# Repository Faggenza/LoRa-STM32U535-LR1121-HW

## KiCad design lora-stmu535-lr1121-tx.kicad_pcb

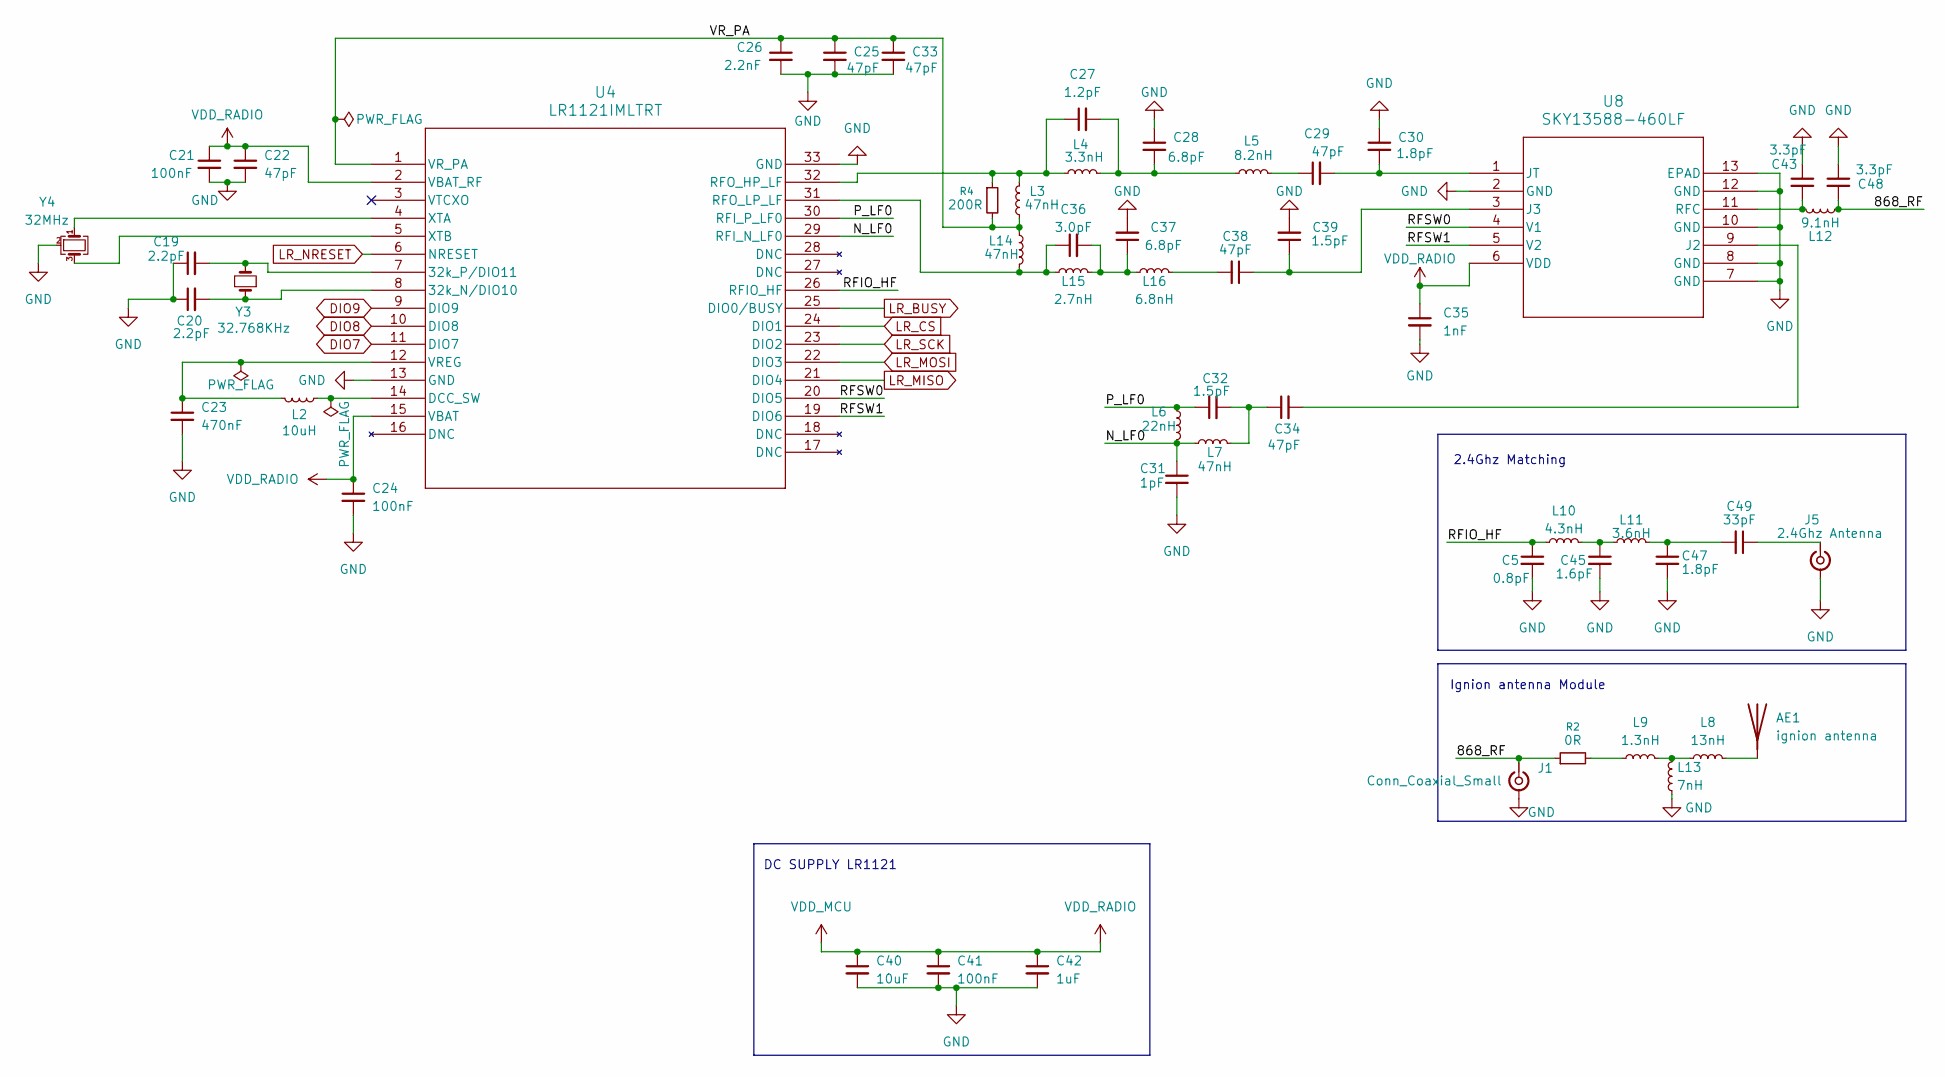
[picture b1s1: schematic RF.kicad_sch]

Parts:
AE1: ignion antenna; igiion_868
C5: 0.8pF; C_0201_0603Metric
C19, C20: 2.2pF; C_0402_1005Metric_Pad0.74x0.62mm_HandSolder
C21, C24, C41: 100nF; C_0402_1005Metric_Pad0.74x0.62mm_HandSolder
C22: 47pF; C_0402_1005Metric_Pad0.74x0.62mm_HandSolder
C23: 470nF; C_0402_1005Metric_Pad0.74x0.62mm_HandSolder
C25, C29, C33, C34, C38: 47pF; C_0201_0603Metric
C26: 2.2nF; C_0201_0603Metric
C27: 1.2pF; C_0201_0603Metric
C28, C37: 6.8pF; C_0201_0603Metric
C30, C47: 1.8pF; C_0201_0603Metric
C31: 1pF; C_0201_0603Metric
C32, C39: 1.5pF; C_0201_0603Metric
C35: 1nF; C_0201_0603Metric
C36: 3.0pF; C_0201_0603Metric
C40: 10uF; C_0603_1608Metric_Pad1.08x0.95mm_HandSolder
C42: 1uF; C_0402_1005Metric_Pad0.74x0.62mm_HandSolder
C43, C48: 3.3pF; C_0201_0603Metric
C45: 1.6pF; C_0201_0603Metric
C49: 33pF; C_0201_0603Metric
J1: Conn_Coaxial_Small; U.FL_Molex_MCRF_73412-0110_Vertical
J5: 2.4Ghz Antenna; U.FL_Molex_MCRF_73412-0110_Vertical
L2: 10uH; L_0603_1608Metric_Pad1.05x0.95mm_HandSolder
L3, L7, L14: 47nH; L_0201_0603Metric
L4: 3.3nH; L_0201_0603Metric
L5: 8.2nH; L_0201_0603Metric
L6: 22nH; L_0201_0603Metric
L8: 13nH; L_0402_1005Metric_Pad0.77x0.64mm_HandSolder
L9: 1.3nH; L_0402_1005Metric_Pad0.77x0.64mm_HandSolder
L10: 4.3nH; L_0201_0603Metric
L11: 3.6nH; L_0201_0603Metric
L12: 9.1nH; L_0201_0603Metric
L13: 7nH; L_0402_1005Metric_Pad0.77x0.64mm_HandSolder
L15: 2.7nH; L_0201_0603Metric
L16: 6.8nH; L_0201_0603Metric
R2: 0R; R_0603_1608Metric_Pad0.98x0.95mm_HandSolder
R4: 200R; R_0201_0603Metric
U4: LR1121IMLTRT; QFN32_5X5_MLP_SEM
U8: SKY13588-460LF; QFN12_SKY-L
Y3: 32.768KHz; Crystal_SMD_2012-2Pin_2.0x1.2mm_HandSoldering
Y4: 32MHz; Crystal_SMD_2016-4Pin_2.0x1.6mm

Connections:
/RF/868_RF: C48.2, J1.1 (In), L12.2, R2.1
/RF/N_LF0: C31.1, L6.2, L7.1, U4.29 (RFI_N_LF0)
/RF/P_LF0: C32.1, L6.1, U4.30 (RFI_P_LF0)
/RF/RFIO_HF: C5.1, L10.1, U4.26 (RFIO_HF)
/RF/RFSW0: U4.20 (DIO5), U8.4 (V1)
/RF/RFSW1: U4.19 (DIO6), U8.5 (V2)
/RF/VR_PA: C25.1, C26.1, C33.1, L3.1, L14.1, R4.2, U4.1 (VR_PA)
DIO7: U4.11 (DIO7); also elsewhere on the board
DIO8: U4.10 (DIO8); also elsewhere on the board
DIO9: U4.9 (DIO9); also elsewhere on the board
GND: AE1.2, C5.2, C19.1, C20.1, C21.2, C22.2, C23.2, C24.2, C25.2, C26.2, C28.1, C30.1, C31.2, C33.2, C35.2, C37.2, C39.2, C40.2, C41.2, C42.2, C43.1, C45.2, C47.2, C48.1, J1.2 (Ext), J5.2 (Ext), L13.1, U4.13 (GND), U4.33 (GND), U8.2 (GND), U8.7 (GND), U8.8 (GND), U8.10 (GND), U8.12 (GND), U8.13 (EPAD), Y4.2 (G), Y4.4 (G); also elsewhere on the board
LR_BUSY: U4.25 (DIO0/BUSY); also elsewhere on the board
LR_CS: U4.24 (DIO1); also elsewhere on the board
LR_MISO: U4.21 (DIO4); also elsewhere on the board
LR_MOSI: U4.22 (DIO3); also elsewhere on the board
LR_NRESET: U4.6 (NRESET); also elsewhere on the board
LR_SCK: U4.23 (DIO2); also elsewhere on the board
unnamed: C27.2, C28.2, L4.2, L5.1
unnamed: C29.1, L5.2
unnamed: C32.2, C34.1, L7.2
unnamed: C36.2, C37.1, L15.2, L16.1
unnamed: C38.2, L16.2
unnamed: C45.1, L10.2, L11.1
unnamed: C47.1, C49.2, L11.2
unnamed: C49.1, J5.1 (In)
unnamed: L8.1, L9.2, L13.2
unnamed: C20.2, U4.8 (32k_N/DIO10), Y3.1
unnamed: C19.2, U4.7 (32k_P/DIO11), Y3.2
unnamed: L2.1, U4.14 (DCC_SW)
unnamed: C27.1, L3.2, L4.1, R4.1, U4.32 (RFO_HP_LF)
unnamed: C36.1, L14.2, L15.1, U4.31 (RFO_LP_LF)
unnamed: C23.1, L2.2, U4.12 (VREG)
unnamed: U4.4 (XTA), Y4.1
unnamed: U4.5 (XTB), Y4.3
unnamed: C34.2, U8.9 (J2)
unnamed: C38.1, C39.1, U8.3 (J3)
unnamed: C29.2, C30.2, U8.1 (JT)
unnamed: C43.2, L12.1, U8.11 (RFC)
VBAT: C21.1, C22.1, C24.1, C35.1, C40.1, C41.1, C42.1, U4.2 (VBAT_RF), U4.15 (VBAT), U8.6 (VDD); also elsewhere on the board

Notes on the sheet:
2.4Ghz Matching
DC SUPPLY LR1121
Ignion antenna Module

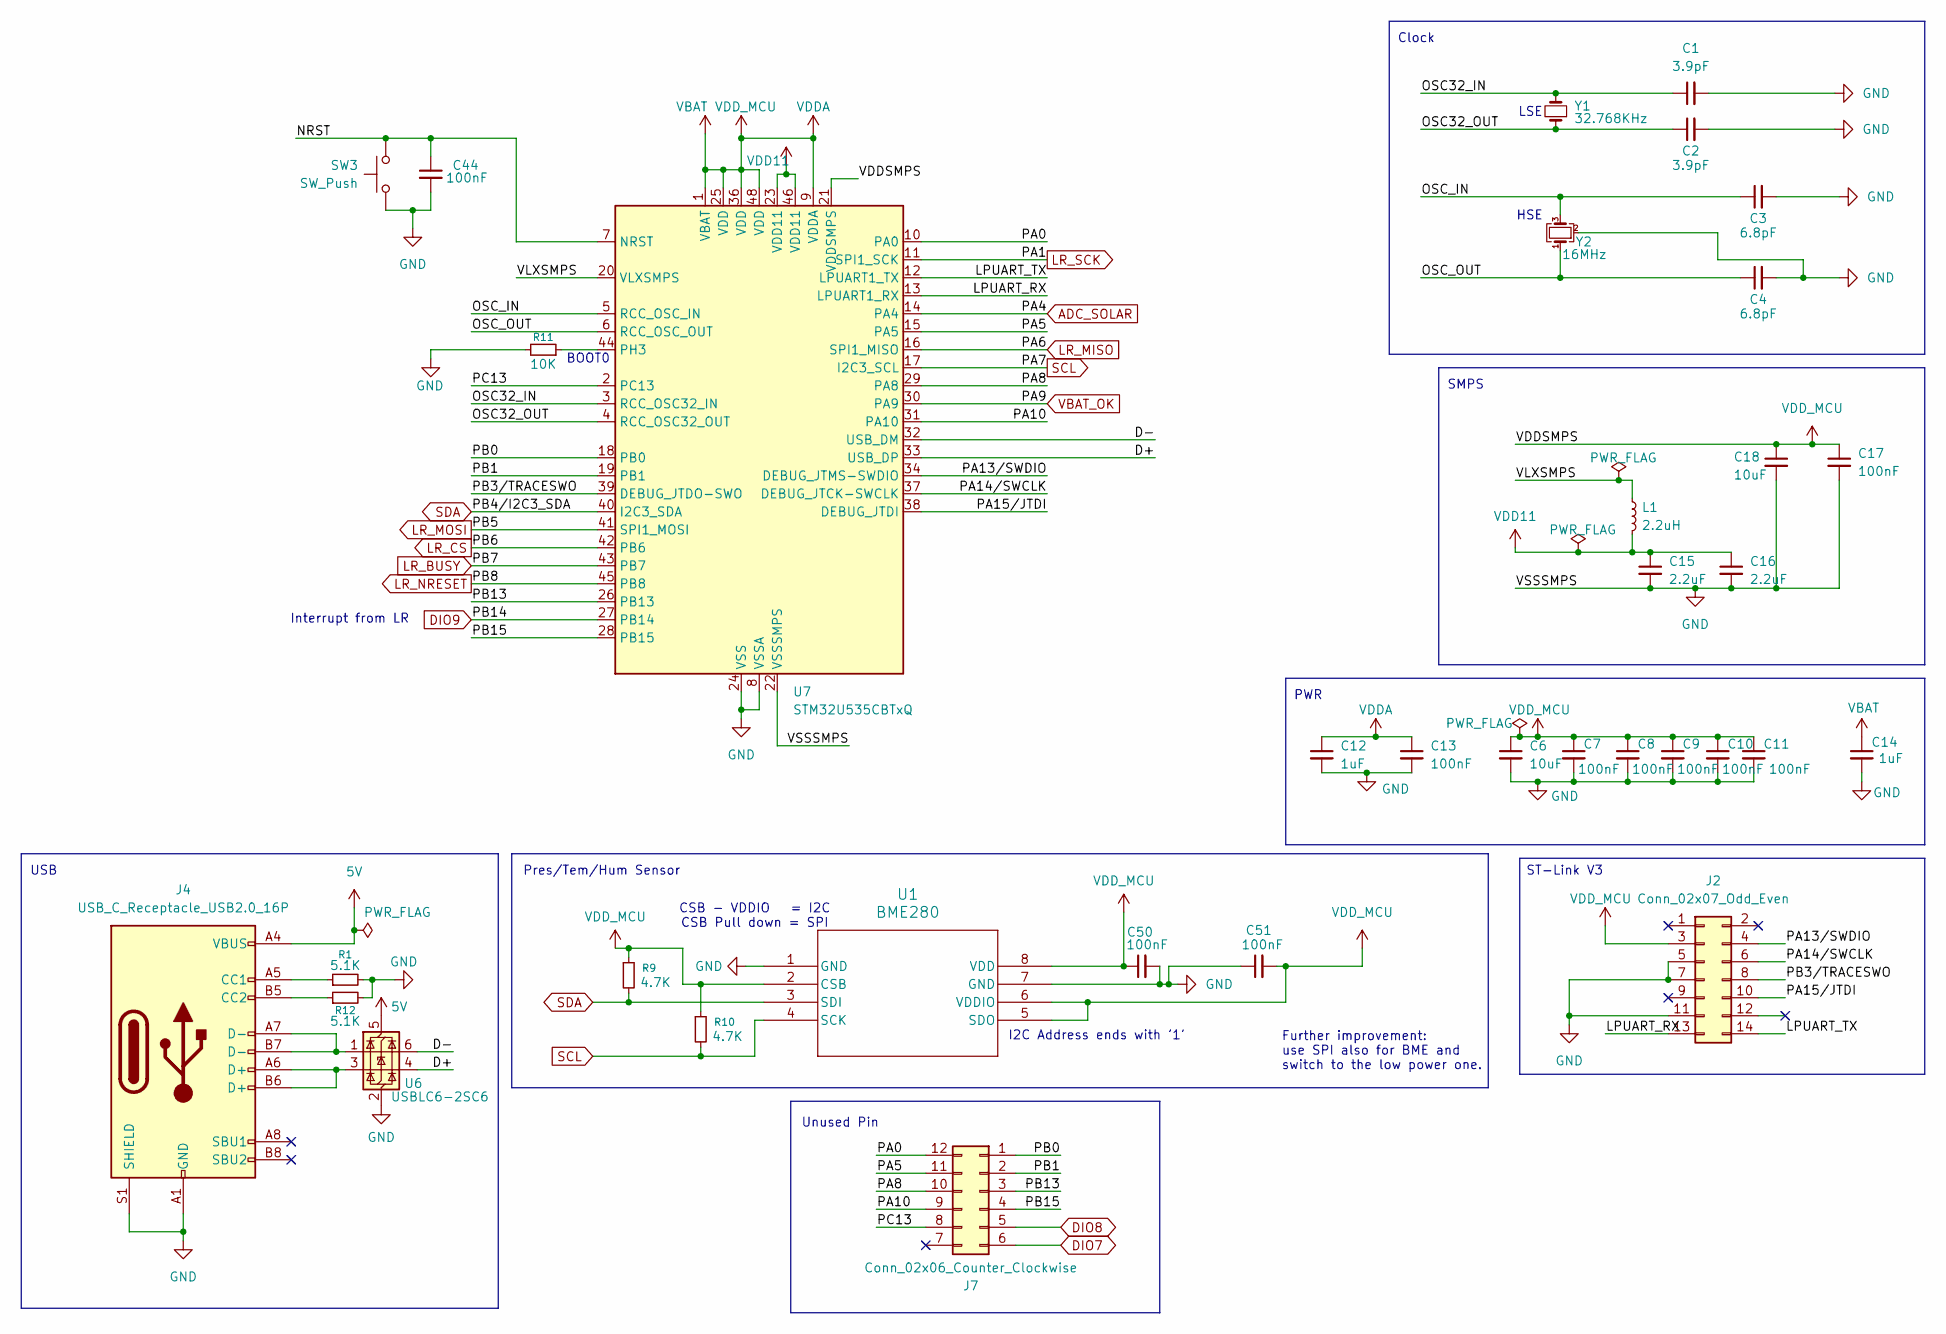
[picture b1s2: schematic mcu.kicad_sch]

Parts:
C1, C2: 3.9pF; C_0402_1005Metric_Pad0.74x0.62mm_HandSolder
C3, C4: 6.8pF; C_0402_1005Metric_Pad0.74x0.62mm_HandSolder
C6, C18: 10uF; C_0603_1608Metric_Pad1.08x0.95mm_HandSolder
C7, C8, C9, C10, C11, C13, C17, C44, C50, C51: 100nF; C_0402_1005Metric_Pad0.74x0.62mm_HandSolder
C12, C14: 1uF; C_0603_1608Metric_Pad1.08x0.95mm_HandSolder
C15, C16: 2.2uF; C_0603_1608Metric_Pad1.08x0.95mm_HandSolder
J2: Conn_02x07_Odd_Even; PinHeader_2x07_P1.27mm_Vertical_SMD
J4: USB_C_Receptacle_USB2.0_16P; USB_C_Receptacle_G-Switch_GT-USB-7010ASV
J7: Conn_02x06_Counter_Clockwise; PinHeader_2x06_P2.54mm_Vertical
L1: 2.2uH; L_0805_2012Metric_Pad1.05x1.20mm_HandSolder
R1, R12: 5.1K; R_0402_1005Metric_Pad0.72x0.64mm_HandSolder
R9, R10: 4.7K; R_0402_1005Metric_Pad0.72x0.64mm_HandSolder
R11: 10K; R_0402_1005Metric_Pad0.72x0.64mm_HandSolder
SW3: SW_Push; SW_SPST_B3U-1000P
U1: BME280; DFN8_0p65_2p5SQ_BOS
U6: USBLC6-2SC6; SOT-666
U7: STM32U535CBTxQ; LQFP-48_7x7mm_P0.5mm
Y1: 32.768KHz; Crystal_SMD_MicroCrystal_CM9V-T1A-2Pin_1.6x1.0mm_HandSolder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
Y2: 16MHz; Crystal_SMD_2016-4Pin_2.0x1.6mm

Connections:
5V: J4.A4 (VBUS), J4.A9 (VBUS), J4.B4 (VBUS), J4.B9 (VBUS), U6.5 (VBUS); also elsewhere on the board
/MCU/D+: U6.4 (I/O2), U7.33 (USB_DP)
/MCU/D-: U6.6 (I/O1), U7.32 (USB_DM)
/MCU/LPUART_RX: J2.13, U7.13 (LPUART1_RX)
/MCU/LPUART_TX: J2.14, U7.12 (LPUART1_TX)
/MCU/NRST: C44.1, SW3.1, U7.7 (NRST)
/MCU/OSC32_IN: C1.1, U7.3 (RCC_OSC32_IN), Y1.2
/MCU/OSC32_OUT: C2.1, U7.4 (RCC_OSC32_OUT), Y1.1
/MCU/OSC_IN: C3.1, U7.5 (RCC_OSC_IN), Y2.3
/MCU/OSC_OUT: C4.1, U7.6 (RCC_OSC_OUT), Y2.1
/MCU/PA0: J7.12, U7.10 (PA0)
/MCU/PA5: J7.11, U7.15 (PA5)
/MCU/PA8: J7.10, U7.29 (PA8)
/MCU/PA10: J7.9, U7.31 (PA10)
/MCU/PA13/SWDIO: J2.4, U7.34 (DEBUG_JTMS-SWDIO)
/MCU/PA14/SWCLK: J2.6, U7.37 (DEBUG_JTCK-SWCLK)
/MCU/PA15/JTDI: J2.10, U7.38 (DEBUG_JTDI)
/MCU/PB0: J7.1, U7.18 (PB0)
/MCU/PB1: J7.2, U7.19 (PB1)
/MCU/PB3/TRACESWO: J2.8, U7.39 (DEBUG_JTDO-SWO)
/MCU/PB13: J7.3, U7.26 (PB13)
/MCU/PB15: J7.4, U7.28 (PB15)
/MCU/PC13: J7.8, U7.2 (PC13)
/MCU/VLXSMPS: L1.1, U7.20 (VLXSMPS)
ADC_SOLAR: U7.14 (PA4); also elsewhere on the board
DIO7: J7.6; also elsewhere on the board
DIO8: J7.5; also elsewhere on the board
DIO9: U7.27 (PB14); also elsewhere on the board
GND: C1.2, C2.2, C3.2, C4.2, C6.2, C7.2, C8.2, C9.2, C10.2, C11.2, C12.2, C13.2, C14.2, C15.2, C16.2, C17.2, C18.2, C44.2, C50.2, C51.1, J2.5, J2.7, J2.11, J4.A1 (GND), J4.A12 (GND), J4.B1 (GND), J4.B12 (GND), J4.S1 (SHIELD), R1.2, R11.2, R12.2, SW3.2, U1.1 (GND), U1.7 (GND), U6.2 (GND), U7.8 (VSSA), U7.22 (VSSSMPS), U7.24 (VSS), U7.35 (VSS), U7.47 (VSS), Y2.2 (G), Y2.4 (G); also elsewhere on the board
LR_BUSY: U7.43 (PB7); also elsewhere on the board
LR_CS: U7.42 (PB6); also elsewhere on the board
LR_MISO: U7.16 (SPI1_MISO); also elsewhere on the board
LR_MOSI: U7.41 (SPI1_MOSI); also elsewhere on the board
LR_NRESET: U7.45 (PB8); also elsewhere on the board
LR_SCK: U7.11 (SPI1_SCK); also elsewhere on the board
unnamed: J4.A5 (CC1), R1.1
unnamed: J4.B5 (CC2), R12.1
unnamed: J4.A6 (D+), J4.B6 (D+), U6.3 (I/O2)
unnamed: J4.A7 (D-), J4.B7 (D-), U6.1 (I/O1)
unnamed: R11.1, U7.44 (PH3)
SCL: R10.2, U1.4 (SCK), U7.17 (I2C3_SCL)
SDA: R9.2, U1.3 (SDI), U7.40 (I2C3_SDA)
VBAT: C6.1, C7.1, C8.1, C9.1, C10.1, C11.1, C12.1, C13.1, C14.1, C17.1, C18.1, C50.1, C51.2, J2.3, R9.1, R10.1, U1.2 (CSB), U1.5 (SDO), U1.6 (VDDIO), U1.8 (VDD), U7.1 (VBAT), U7.9 (VDDA), U7.21 (VDDSMPS), U7.25 (VDD), U7.36 (VDD), U7.48 (VDD); also elsewhere on the board
VBAT_OK: U7.30 (PA9); also elsewhere on the board
VDD11: C15.1, C16.1, L1.2, U7.23 (VDD11), U7.46 (VDD11)

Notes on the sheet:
Further improvement: use SPI also for BME and switch to the low power one.
BOOT0
I2C Address ends with '1'
Clock
LSE
HSE
SMPS
Interrupt from LR
CSB - VDDIO = I2C CSB Pull down = SPI
ST-Link V3
Pres/Tem/Hum Sensor
PWR
Unused Pin
USB

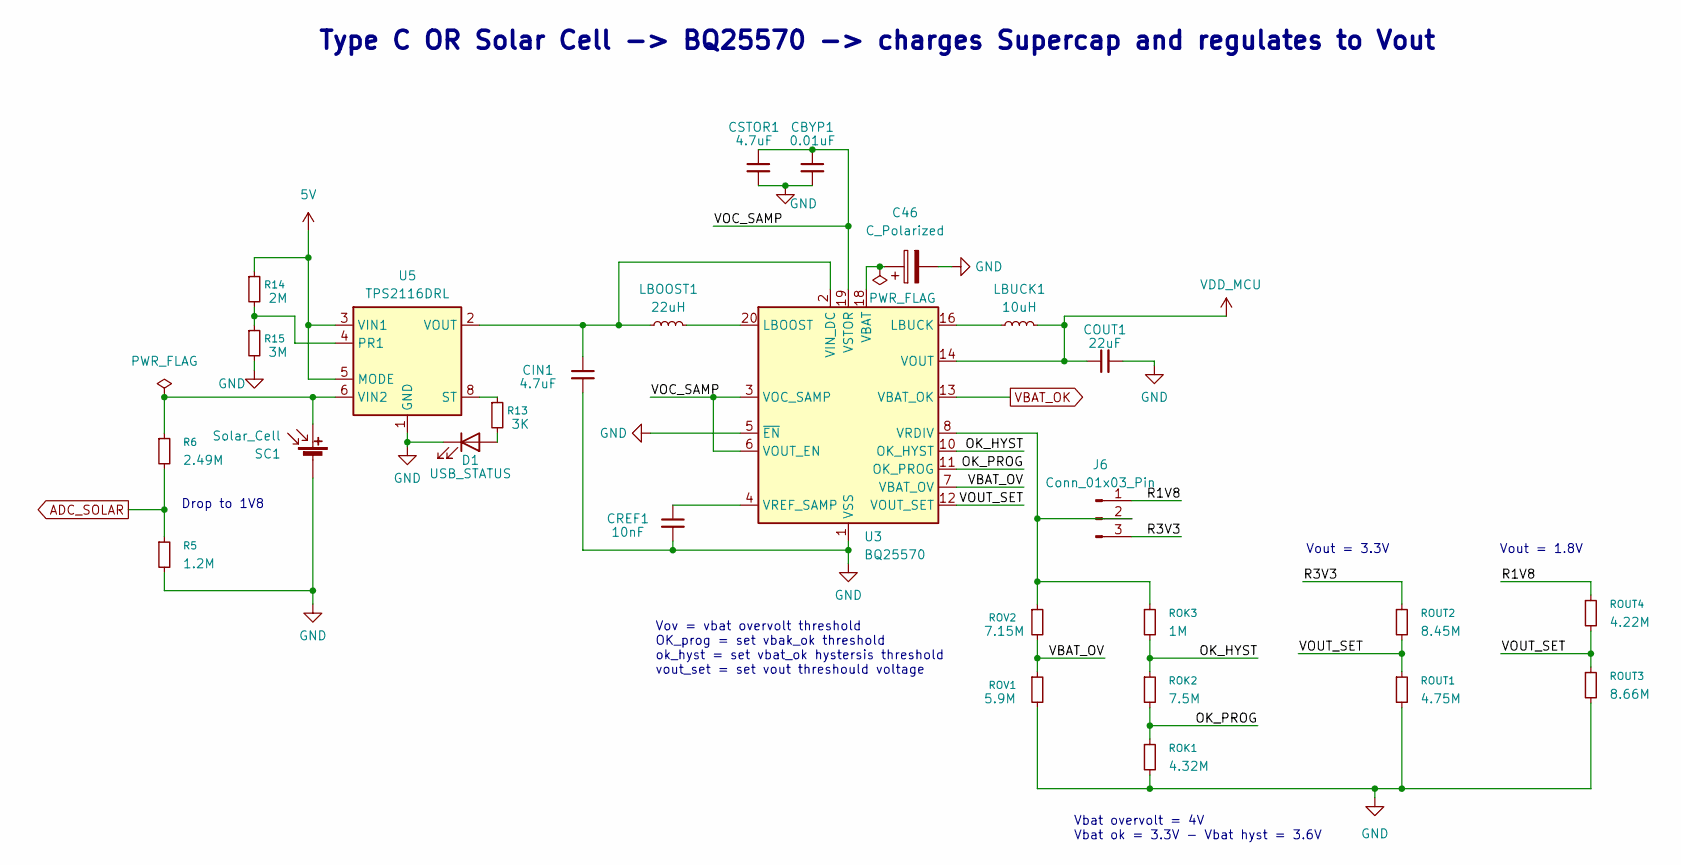
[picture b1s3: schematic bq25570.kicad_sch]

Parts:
C46: C_Polarized; PinHeader_1x02_P2.54mm_Vertical
CBYP1: 0.01uF; C_0402_1005Metric_Pad0.74x0.62mm_HandSolder
CIN1: 4.7uF; C_0603_1608Metric_Pad1.08x0.95mm_HandSolder
COUT1: 22uF; C_0603_1608Metric_Pad1.08x0.95mm_HandSolder
CREF1: 10nF; C_0402_1005Metric_Pad0.74x0.62mm_HandSolder
CSTOR1: 4.7uF; C_0603_1608Metric_Pad1.08x0.95mm_HandSolder
D1: USB_STATUS; LED_0402_1005Metric_Pad0.77x0.64mm_HandSolder
J6: Conn_01x03_Pin; PinHeader_1x03_P2.54mm_Vertical
LBOOST1: 22uH; L_0402_1005Metric_Pad0.77x0.64mm_HandSolder
LBUCK1: 10uH; L_0603_1608Metric_Pad1.05x0.95mm_HandSolder
R5: 1.2M; R_0402_1005Metric_Pad0.72x0.64mm_HandSolder
R6: 2.49M; R_0402_1005Metric_Pad0.72x0.64mm_HandSolder
R13: 3K; R_0402_1005Metric_Pad0.72x0.64mm_HandSolder
R14: 2M; R_0402_1005Metric_Pad0.72x0.64mm_HandSolder
R15: 3M; R_0402_1005Metric_Pad0.72x0.64mm_HandSolder
ROK1: 4.32M; R_0402_1005Metric_Pad0.72x0.64mm_HandSolder
ROK2: 7.5M; R_0402_1005Metric_Pad0.72x0.64mm_HandSolder
ROK3: 1M; R_0402_1005Metric_Pad0.72x0.64mm_HandSolder
ROUT1: 4.75M; R_0402_1005Metric_Pad0.72x0.64mm_HandSolder
ROUT2: 8.45M; R_0402_1005Metric_Pad0.72x0.64mm_HandSolder
ROUT3: 8.66M; R_0402_1005Metric_Pad0.72x0.64mm_HandSolder
ROUT4: 4.22M; R_0402_1005Metric_Pad0.72x0.64mm_HandSolder
ROV1: 5.9M; R_0402_1005Metric_Pad0.72x0.64mm_HandSolder
ROV2: 7.15M; R_0402_1005Metric_Pad0.72x0.64mm_HandSolder
SC1: Solar_Cell; PinHeader_1x02_P2.54mm_Vertical
U3: BQ25570; QFN-20-1EP_3.5x3.5mm_P0.5mm_EP2x2mm
U5: TPS2116DRL; SOT-583-8

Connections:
5V: R14.1, U5.3 (VIN1), U5.5 (MODE); also elsewhere on the board
/BQ25570/OK_HYST: ROK2.1, ROK3.2, U3.10 (OK_HYST)
/BQ25570/OK_PROG: ROK1.1, ROK2.2, U3.11 (OK_PROG)
/BQ25570/R1V8: J6.1 (1.8), ROUT4.1
/BQ25570/R3V3: J6.3 (3.3), ROUT2.1
/BQ25570/VBAT_OV: ROV1.1, ROV2.2, U3.7 (VBAT_OV)
/BQ25570/VOC_SAMP: CBYP1.1, CSTOR1.1, U3.3 (VOC_SAMP), U3.6 (VOUT_EN), U3.19 (VSTOR)
/BQ25570/VOUT_SET: ROUT1.1, ROUT2.2, ROUT3.1, ROUT4.2, U3.12 (VOUT_SET)
ADC_SOLAR: R5.1, R6.2; also elsewhere on the board
GND: C46.2, CBYP1.2, CIN1.2, COUT1.2, CREF1.2, CSTOR1.2, D1.1 (K), R5.2, R15.2, ROK1.2, ROUT1.2, ROUT3.2, ROV1.2, SC1.2 (-), U3.1 (VSS), U3.5 (~EN), U3.9 (VSS), U3.15 (VSS), U3.17 (VSS), U3.21 (VSS), U5.1 (GND); also elsewhere on the board
unnamed: D1.2 (A), R13.2
unnamed: J6.2, ROK3.1, ROV2.1, U3.8 (VRDIV)
unnamed: R6.1, SC1.1 (+), U5.6 (VIN2)
unnamed: LBOOST1.2, U3.20 (LBOOST)
unnamed: LBUCK1.1, U3.16 (LBUCK)
unnamed: C46.1, U3.18 (VBAT)
unnamed: CIN1.1, LBOOST1.1, U3.2 (VIN_DC), U5.2 (VOUT), U5.7 (VOUT)
unnamed: CREF1.1, U3.4 (VREF_SAMP)
unnamed: R14.2, R15.1, U5.4 (PR1)
unnamed: R13.1, U5.8 (ST)
VBAT: COUT1.1, LBUCK1.2, U3.14 (VOUT); also elsewhere on the board
VBAT_OK: U3.13 (VBAT_OK); also elsewhere on the board

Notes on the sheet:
Vout = 3.3V
Drop to 1V8
Vout = 1.8V
Type C OR Solar Cell -> BQ25570 -> charges Supercap and regulates to Vout
Vbat overvolt = 4V Vbat ok = 3.3V - Vbat hyst = 3.6V
Vov = vbat overvolt threshold OK_prog = set vbak_ok threshold ok_hyst = set vbat_ok hystersis threshold vout_set = set vout threshould voltage

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
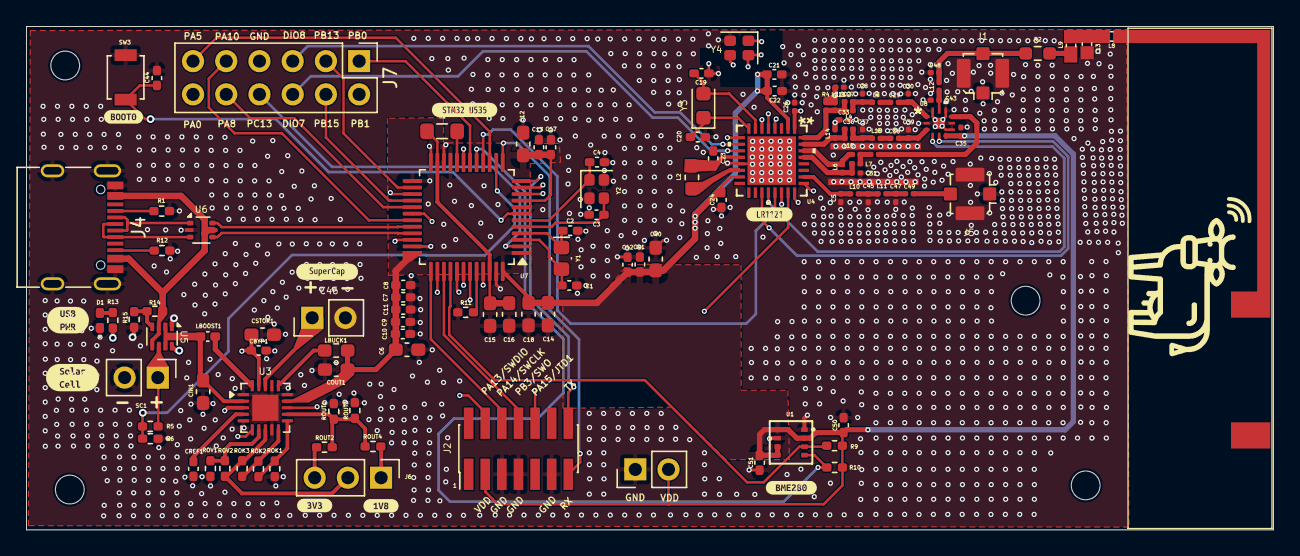
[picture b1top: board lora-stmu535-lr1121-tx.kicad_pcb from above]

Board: 4 copper layers, 95.3 x 38.5 mm, 125 parts (0 on the bottom side), 92 nets.

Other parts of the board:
kibuzzard-69E8EEEB: G***; kibuzzard-69E8EEEB
kibuzzard-69E8EEF7: G***; kibuzzard-69E8EEF7
kibuzzard-69E8EF24: G***; kibuzzard-69E8EF24
kibuzzard-69E8EF49: G***; kibuzzard-69E8EF49
kibuzzard-69E8EF58: G***; kibuzzard-69E8EF58
kibuzzard-69E8FA9E: G***; kibuzzard-69E8FA9E
kibuzzard-69EF5185: G***; kibuzzard-69EF5185
kibuzzard-69F35B1F: G***; kibuzzard-69F35B1F
kibuzzard-69F35B2E: G***; kibuzzard-69F35B2E

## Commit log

2026-04-17 add device schematic
2026-04-20 footprint assignment
2026-04-22 RF and initial routing
2026-04-22 fix DRC errors and antenna
2026-04-24 labeling and via placing
2026-04-24 changed RF switch in schematics, todo in pcb
2026-04-27 separated matching lines
2026-04-30 fix smtp line and minor errors
2026-05-04 V0.1
